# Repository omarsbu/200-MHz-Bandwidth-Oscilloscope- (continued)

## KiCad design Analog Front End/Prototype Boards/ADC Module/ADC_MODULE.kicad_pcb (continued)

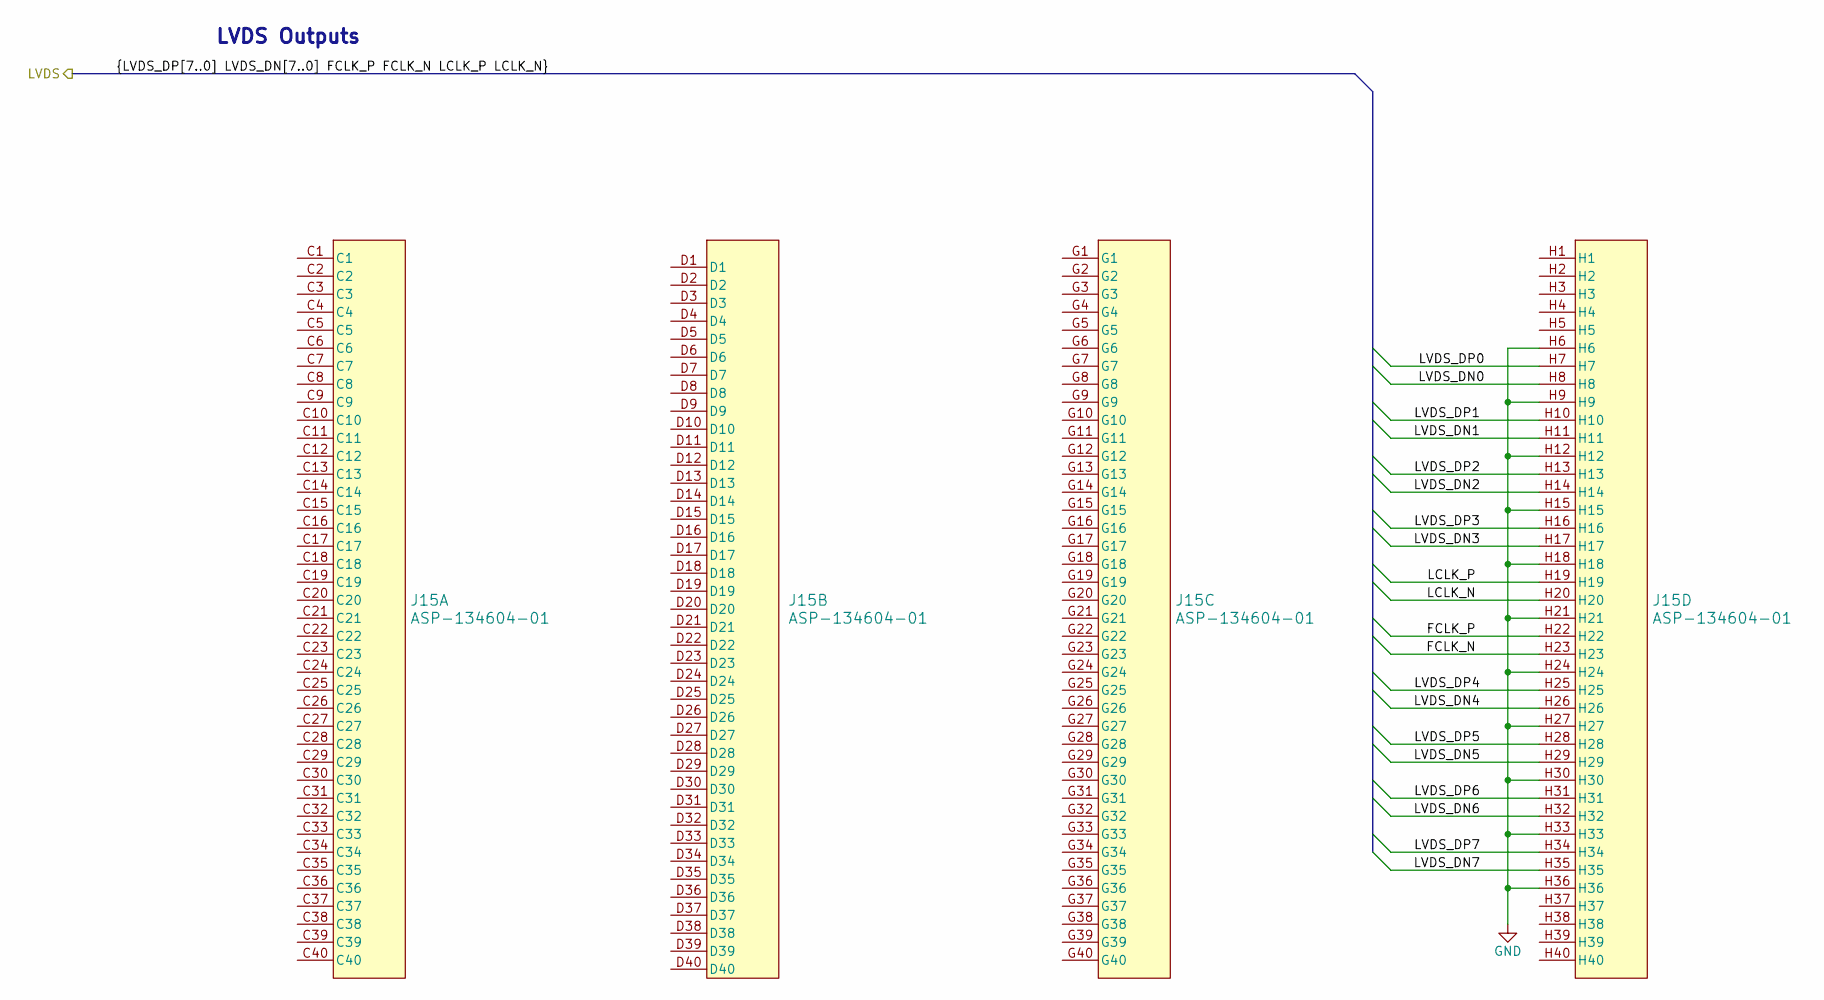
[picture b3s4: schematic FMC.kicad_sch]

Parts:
J15: ASP-134604-01; SAMTEC_ASP-134604-01

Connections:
/ADC/FCLK_N: J15.H23; also elsewhere on the board
/ADC/FCLK_P: J15.H22; also elsewhere on the board
/ADC/LCLK_N: J15.H20; also elsewhere on the board
/ADC/LCLK_P: J15.H19; also elsewhere on the board
/ADC/LVDS_DN0: J15.H8; also elsewhere on the board
/ADC/LVDS_DN1: J15.H11; also elsewhere on the board
/ADC/LVDS_DN2: J15.H14; also elsewhere on the board
/ADC/LVDS_DN3: J15.H17; also elsewhere on the board
/ADC/LVDS_DN4: J15.H26; also elsewhere on the board
/ADC/LVDS_DN5: J15.H29; also elsewhere on the board
/ADC/LVDS_DN6: J15.H32; also elsewhere on the board
/ADC/LVDS_DN7: J15.H35; also elsewhere on the board
/ADC/LVDS_DP0: J15.H7; also elsewhere on the board
/ADC/LVDS_DP1: J15.H10; also elsewhere on the board
/ADC/LVDS_DP2: J15.H13; also elsewhere on the board
/ADC/LVDS_DP3: J15.H16; also elsewhere on the board
/ADC/LVDS_DP4: J15.H25; also elsewhere on the board
/ADC/LVDS_DP5: J15.H28; also elsewhere on the board
/ADC/LVDS_DP6: J15.H31; also elsewhere on the board
/ADC/LVDS_DP7: J15.H34; also elsewhere on the board
GND: J15.H6, J15.H9, J15.H12, J15.H15, J15.H18, J15.H21, J15.H24, J15.H27, J15.H30, J15.H33, J15.H36; also elsewhere on the board

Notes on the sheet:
LVDS Outputs

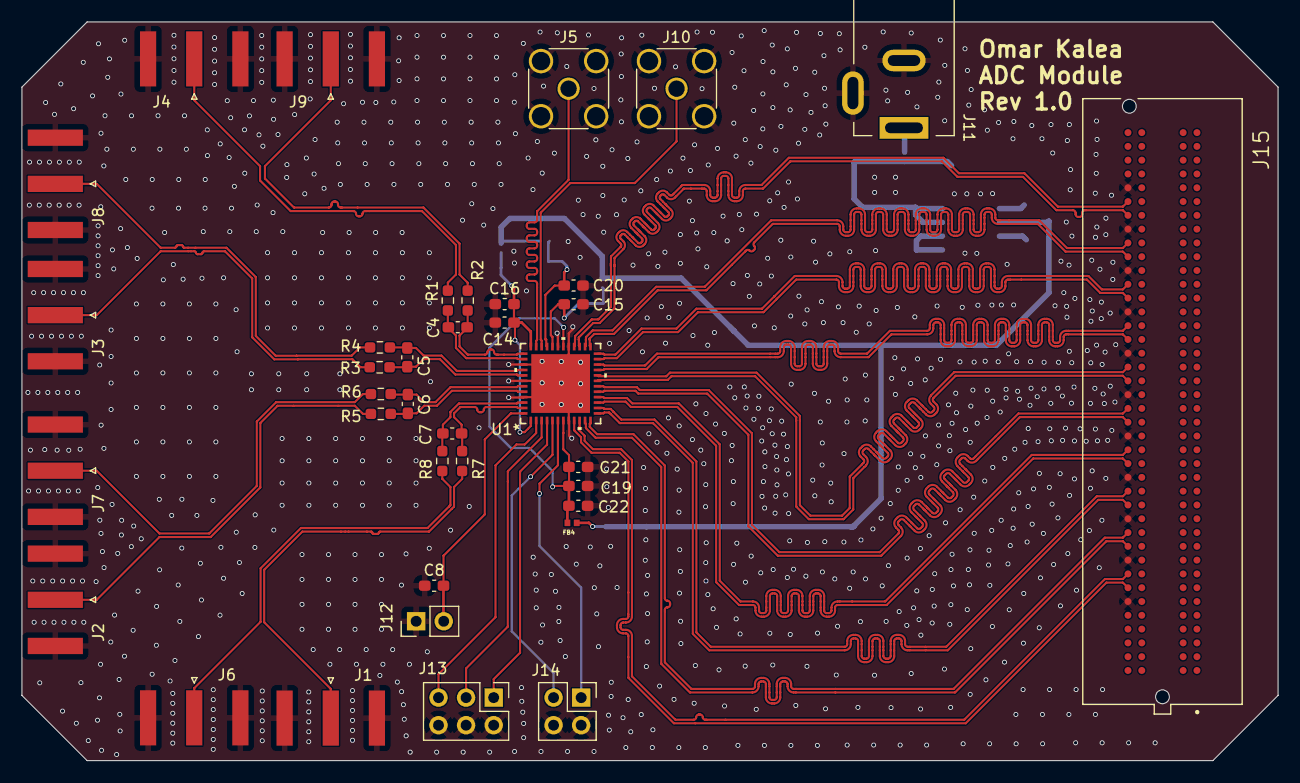
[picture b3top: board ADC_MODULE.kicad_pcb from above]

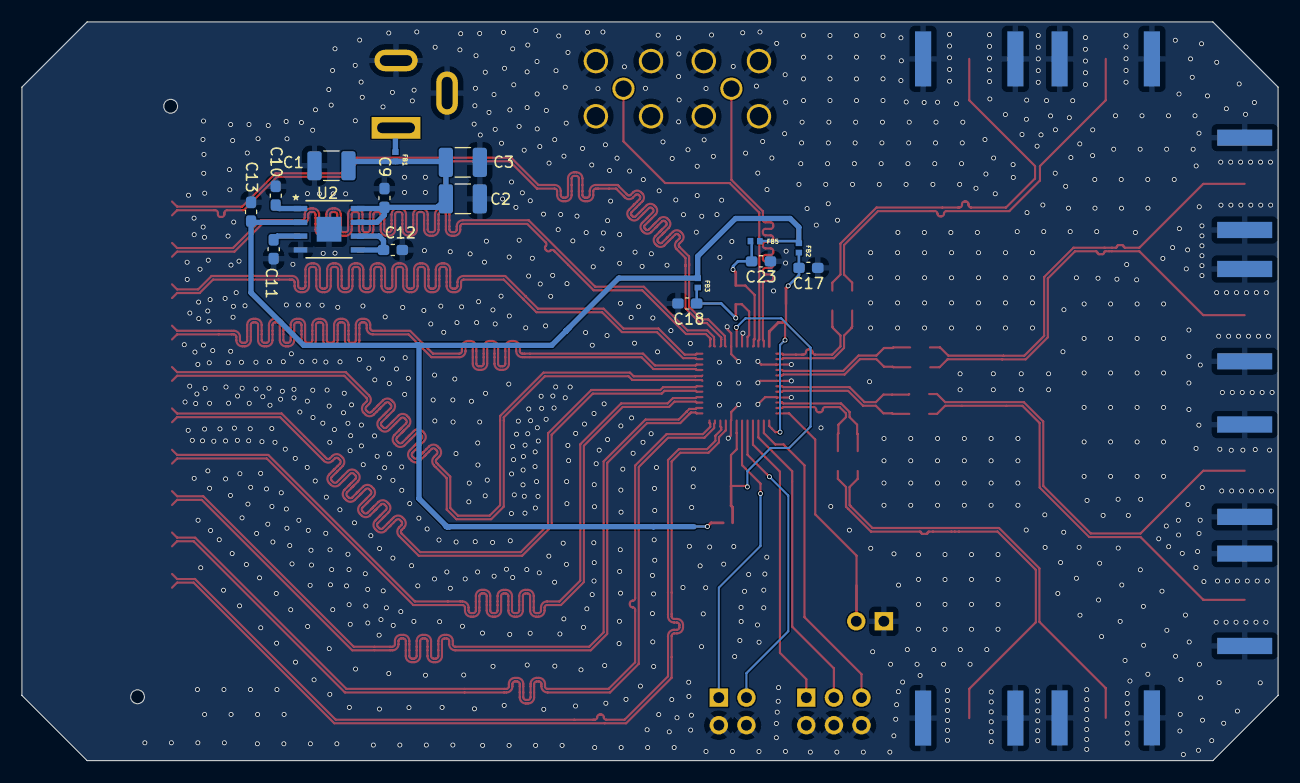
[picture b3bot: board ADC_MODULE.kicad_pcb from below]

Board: 4 copper layers, 115.7 x 68.0 mm, 53 parts (16 on the bottom side), 55 nets.

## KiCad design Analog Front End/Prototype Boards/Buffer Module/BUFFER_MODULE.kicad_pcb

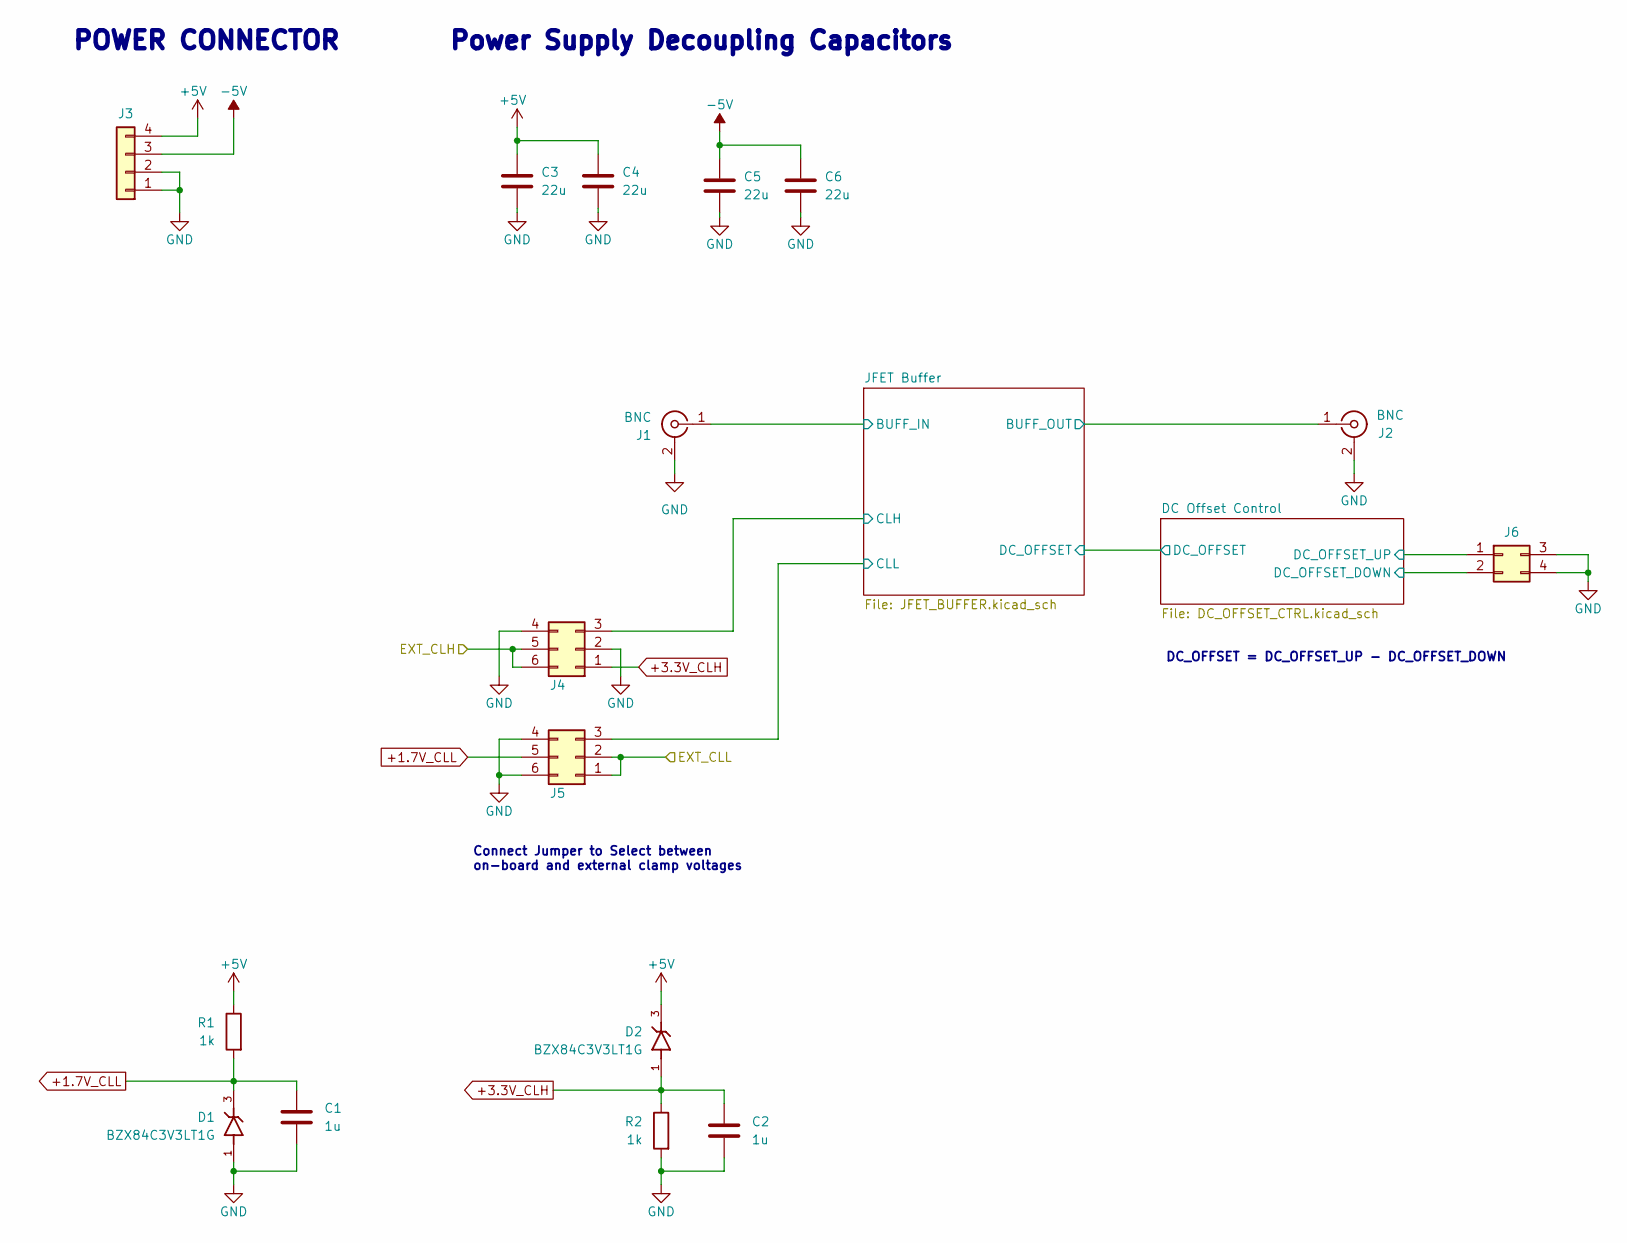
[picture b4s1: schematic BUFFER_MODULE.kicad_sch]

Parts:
C1, C2: 1u; C_0603_1608Metric
C3, C4, C5, C6: 22u; C_1210_3225Metric_Pad1.33x2.70mm_HandSolder
D1, D2: BZX84C3V3LT1G; SOT95P240X111-3N; PARTREV 23
J1, J2: BNC; CONN_73100-0105_MOL
J3: Conn_01x04; PinHeader_2x02_P2.54mm_Vertical
J4, J5: Conn_02x03_Counter_Clockwise; PinHeader_2x03_P2.54mm_Vertical
J6: Conn_02x02_Top_Bottom; PinHeader_2x02_P2.54mm_Vertical
R1, R2: 1k; R_0603_1608Metric

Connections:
+1.7V_CLL: C1.2, D1.3, J5.5, R1.2
+3.3V_CLH: C2.2, D2.1, J4.1, R2.1
+5V: C3.1, C4.1, D2.3, J3.4, R1.1; also elsewhere on the board
-5V: C5.1, C6.1, J3.3; also elsewhere on the board
/DC Offset Control/DC_OFFSET_DOWN: J6.2; also elsewhere on the board
/DC Offset Control/DC_OFFSET_UP: J6.1; also elsewhere on the board
/EXT_CLH: J4.5, J4.6
/EXT_CLL: J5.1, J5.2
/JFET Buffer/BUFF_IN: J1.1 (In); also elsewhere on the board
/JFET Buffer/BUFF_OUT: J2.1 (In); also elsewhere on the board
/JFET Buffer/CLH: J4.3; also elsewhere on the board
/JFET Buffer/CLL: J5.3; also elsewhere on the board
GND: C1.1, C2.1, C3.2, C4.2, C5.2, C6.2, D1.1, D1.2, D2.2, J1.2 (Ext), J1.3, J2.2 (Ext), J2.3, J3.1, J3.2, J4.2, J4.4, J5.4, J5.6, J6.3, J6.4, R2.2; also elsewhere on the board

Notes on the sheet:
Connect Jumper to Select between on-board and external clamp voltages
Power Supply Decoupling Capacitors
DC_OFFSET = DC_OFFSET_UP - DC_OFFSET_DOWN
POWER CONNECTOR

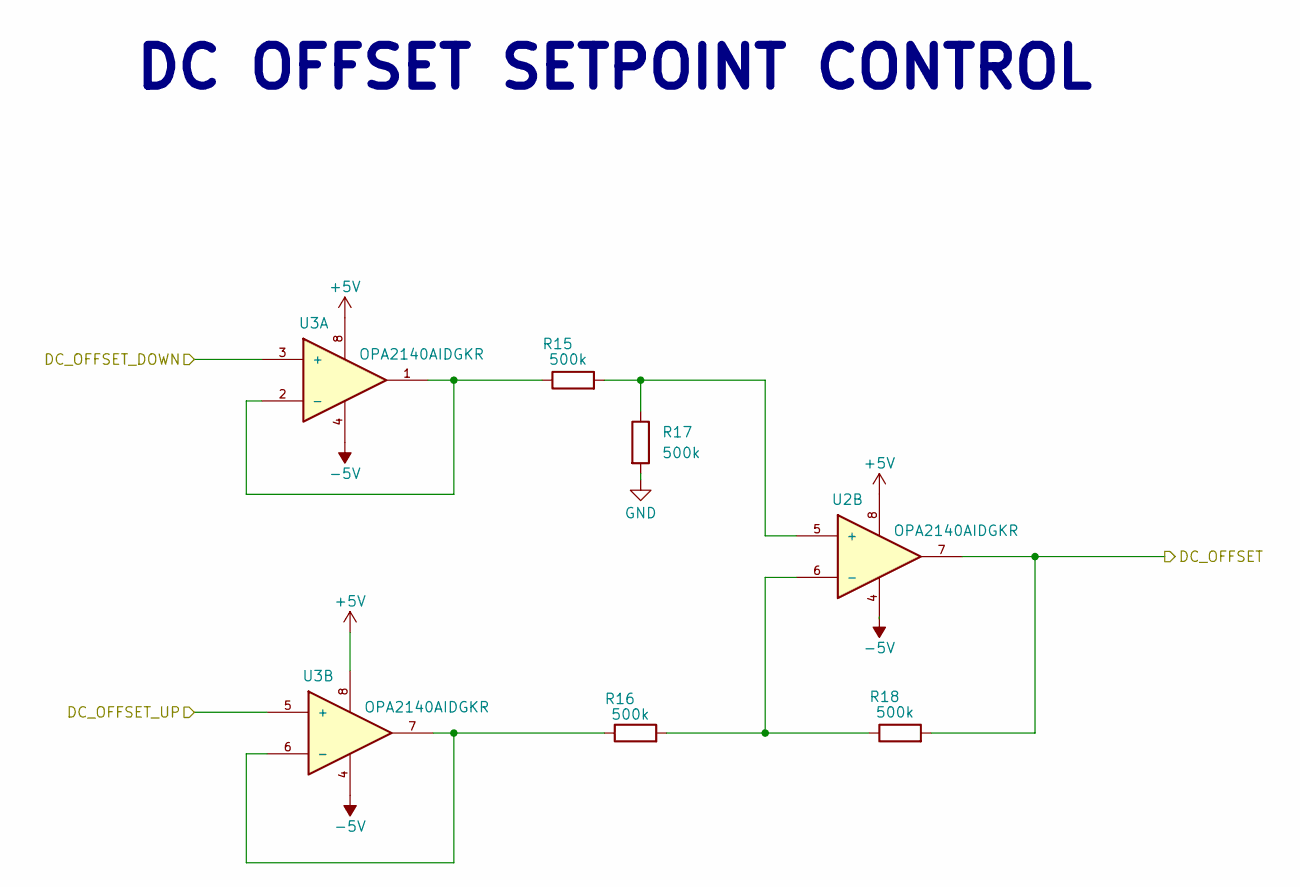
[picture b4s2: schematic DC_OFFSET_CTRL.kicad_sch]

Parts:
R15, R16, R17, R18: 500k; R_0603_1608Metric
U2, U3: OPA2140AIDGKR; DGK8; DigiKey_Part_Number 296-46321-1-ND

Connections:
+5V: U2.8, U3.8; also elsewhere on the board
-5V: U2.4, U3.4; also elsewhere on the board
/DC Offset Control/DC_OFFSET: R18.2, U2.7; also elsewhere on the board
/DC Offset Control/DC_OFFSET_DOWN: U3.3 (+); also elsewhere on the board
/DC Offset Control/DC_OFFSET_UP: U3.5 (+); also elsewhere on the board
GND: R17.2; also elsewhere on the board
unnamed: R15.2, R17.1, U2.5 (+)
unnamed: R16.2, R18.1, U2.6 (-)
unnamed: R15.1, U3.1, U3.2 (-)
unnamed: R16.1, U3.6 (-), U3.7

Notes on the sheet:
DC OFFSET SETPOINT CONTROL

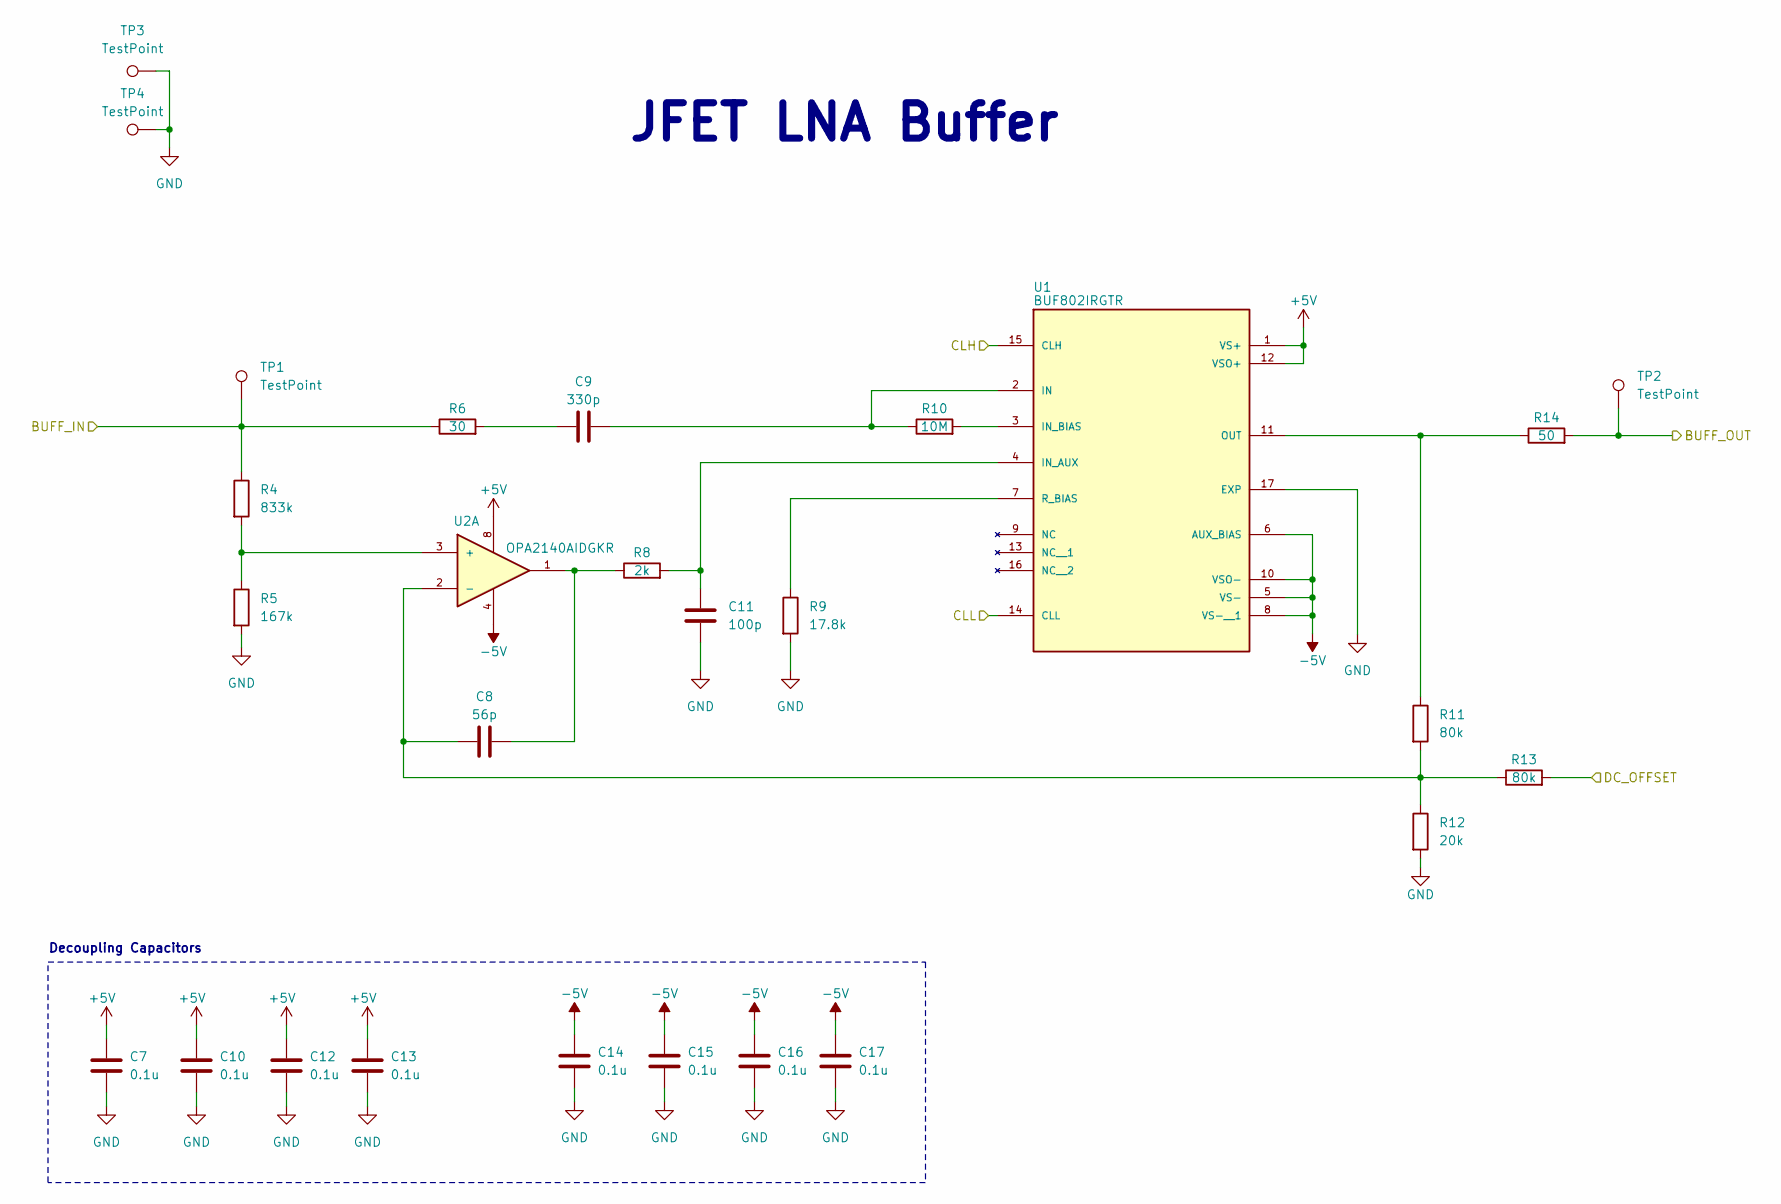
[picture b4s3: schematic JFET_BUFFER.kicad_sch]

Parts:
C7, C10, C12, C13, C14, C15, C16, C17: 0.1u; C_0603_1608Metric
C8: 56p; C_0603_1608Metric
C9: 330p; C_0603_1608Metric
C11: 100p; C_0603_1608Metric
R4: 833k; R_0603_1608Metric
R5: 167k; R_0603_1608Metric
R6: 30; R_0603_1608Metric
R8: 2k; R_0603_1608Metric
R9: 17.8k; R_0603_1608Metric
R10: 10M; R_0603_1608Metric
R11, R13: 80k; R_0603_1608Metric
R12: 20k; R_0603_1608Metric
R14: 50; R_0603_1608Metric
TP1, TP2, TP3, TP4: TestPoint; TestPoint_Pad_1.5x1.5mm
U1: BUF802IRGTR; VQFN16_RGT_TEX; PARTREV C
U2: OPA2140AIDGKR; DGK8; DigiKey_Part_Number 296-46321-1-ND

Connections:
+5V: C7.1, C10.1, C12.1, C13.1, U1.1 (VS+), U1.12 (VSO+), U2.8; also elsewhere on the board
-5V: C14.1, C15.1, C16.1, C17.1, U1.5 (VS-), U1.6 (AUX_BIAS), U1.8 (VS-__1), U1.10 (VSO-), U2.4; also elsewhere on the board
/DC Offset Control/DC_OFFSET: R13.2; also elsewhere on the board
/JFET Buffer/BUFF_IN: R4.1, R6.1, TP1.1; also elsewhere on the board
/JFET Buffer/BUFF_OUT: R14.2, TP2.1; also elsewhere on the board
/JFET Buffer/CLH: U1.15 (CLH); also elsewhere on the board
/JFET Buffer/CLL: U1.14 (CLL); also elsewhere on the board
GND: C7.2, C10.2, C11.1, C12.2, C13.2, C14.2, C15.2, C16.2, C17.2, R5.2, R9.2, R12.2, TP3.1, TP4.1, U1.17 (EXP); also elsewhere on the board
unnamed: C8.2, R8.1, U2.1
unnamed: C9.1, R6.2
unnamed: C9.2, R10.1, U1.2 (IN)
unnamed: C11.2, R8.2, U1.4 (IN_AUX)
unnamed: R10.2, U1.3 (IN_BIAS)
unnamed: R11.1, R14.1, U1.11 (OUT)
unnamed: R9.1, U1.7 (R_BIAS)
unnamed: R4.2, R5.1, U2.3 (+)
unnamed: C8.1, R11.2, R12.1, R13.1, U2.2 (-)

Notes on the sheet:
JFET LNA Buffer
Decoupling Capacitors

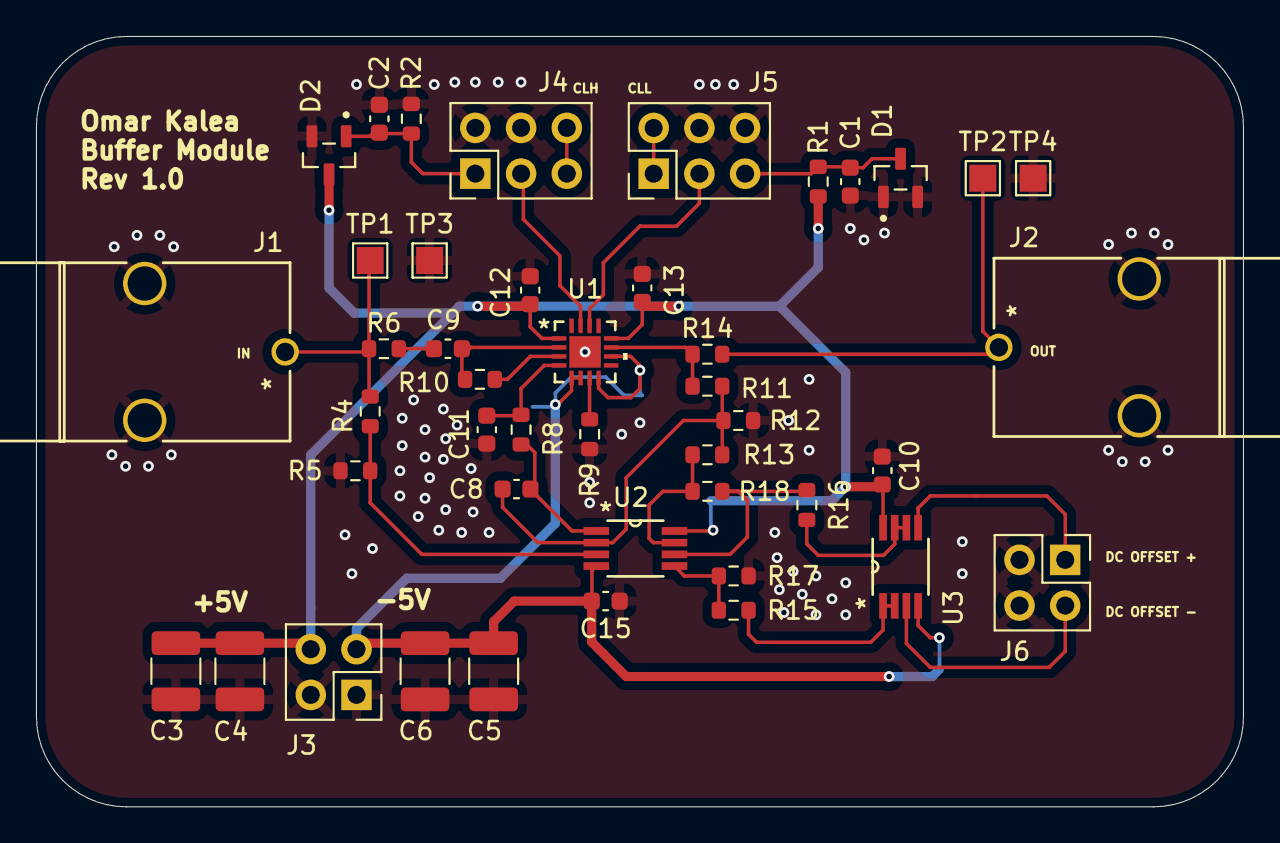
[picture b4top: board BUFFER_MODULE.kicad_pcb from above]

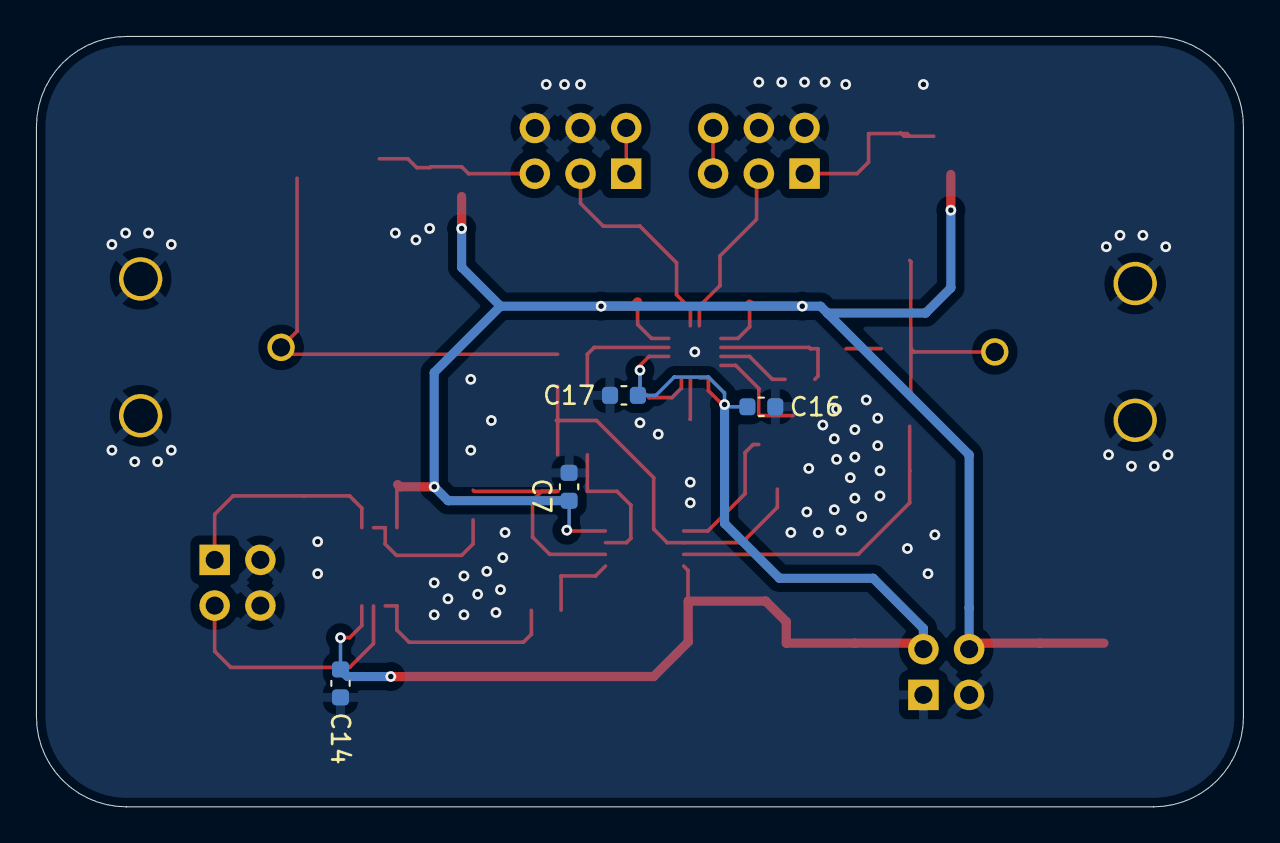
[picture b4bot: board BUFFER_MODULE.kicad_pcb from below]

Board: 4 copper layers, 67.1 x 42.8 mm, 48 parts (4 on the bottom side), 27 nets.

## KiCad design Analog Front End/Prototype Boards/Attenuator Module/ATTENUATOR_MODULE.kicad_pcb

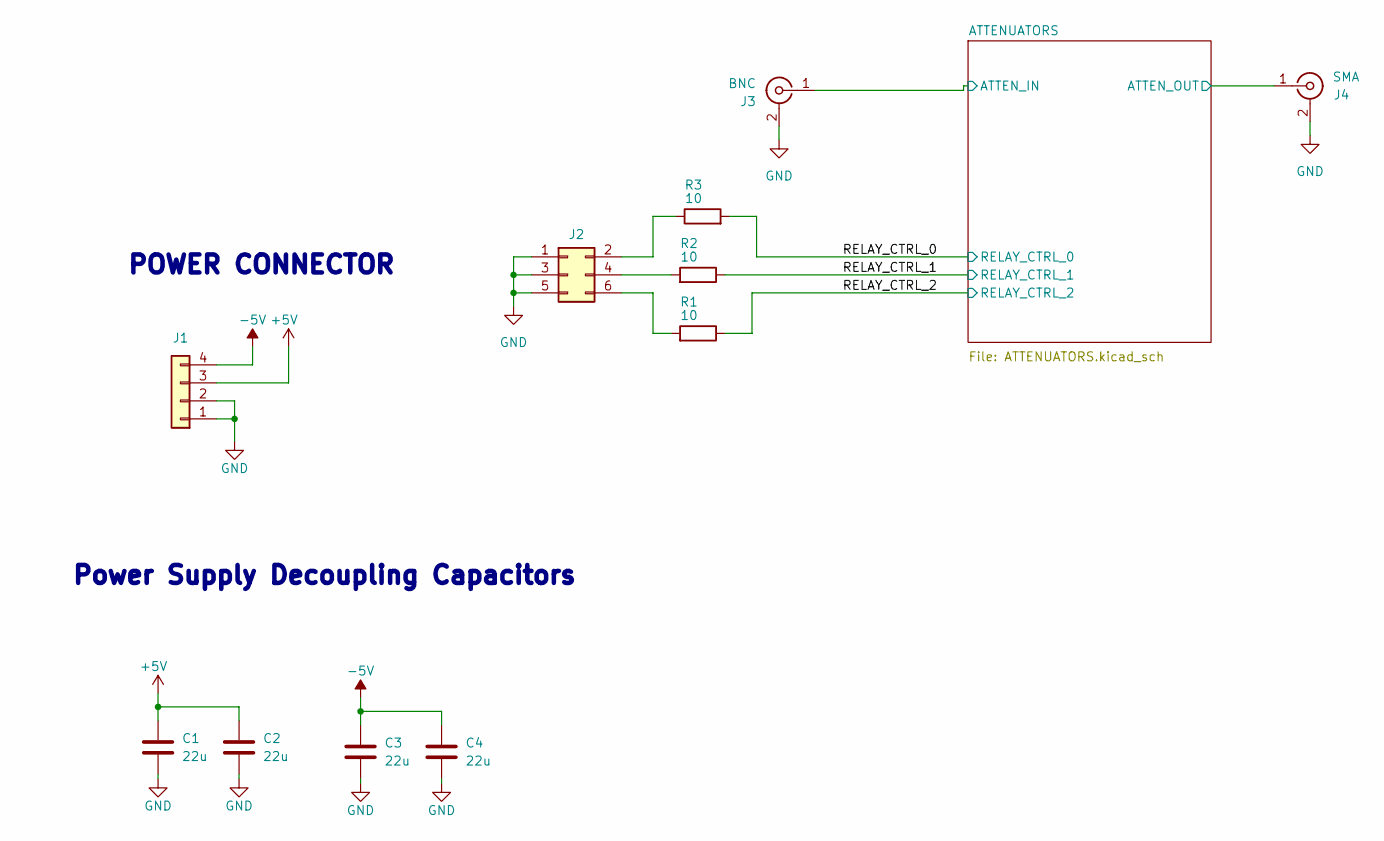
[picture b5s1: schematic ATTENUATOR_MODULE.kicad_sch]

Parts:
C1, C2, C3, C4: 22u; C_1210_3225Metric_Pad1.33x2.70mm_HandSolder
J1: Conn_01x04; PinHeader_2x02_P2.54mm_Vertical
J2: Conn_02x03_Odd_Even; PinHeader_2x03_P2.54mm_Vertical
J3: BNC; CONN_73100-0105_MOL
J4: SMA; SAMTEC_SMA-J-P-H-ST-EM1
R1, R2, R3: 10; R_0603_1608Metric

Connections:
+5V: C1.1, C2.1, J1.3; also elsewhere on the board
-5V: C3.1, C4.1, J1.4; also elsewhere on the board
/ATTENUATORS/ATTEN_IN: J3.1 (In); also elsewhere on the board
/ATTENUATORS/ATTEN_OUT: J4.1 (In); also elsewhere on the board
/RELAY_CTRL_0: R3.2; also elsewhere on the board
/RELAY_CTRL_1: R2.1; also elsewhere on the board
/RELAY_CTRL_2: R1.1; also elsewhere on the board
GND: C1.2, C2.2, C3.2, C4.2, J1.1, J1.2, J2.1, J2.3, J2.5, J3.2 (Ext), J3.3, J4.2 (Ext), J4.2_1, J4.2_2, J4.3_1, J4.3_2; also elsewhere on the board
unnamed: J2.2, R3.1
unnamed: J2.4, R2.2
unnamed: J2.6, R1.2

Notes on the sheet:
POWER CONNECTOR
Power Supply Decoupling Capacitors

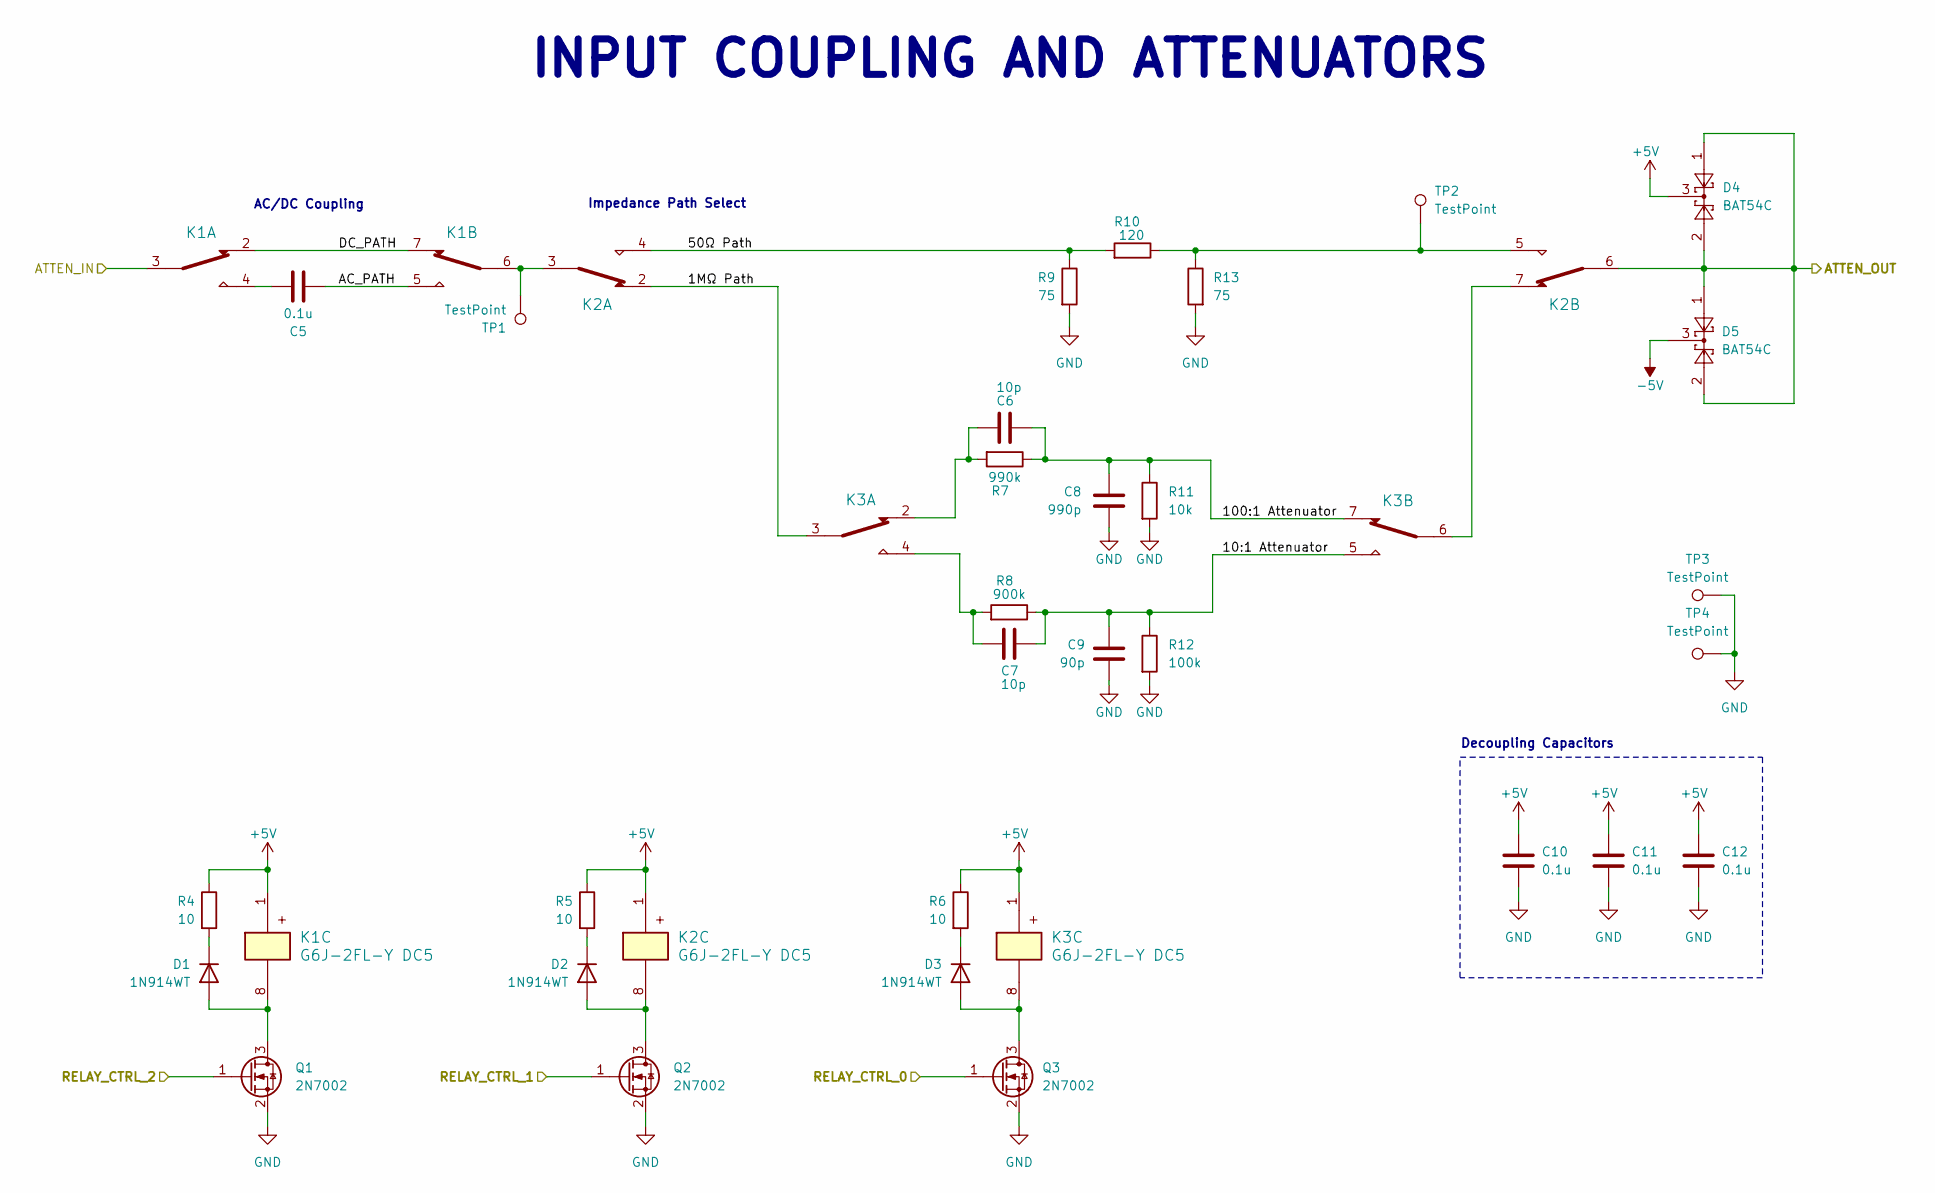
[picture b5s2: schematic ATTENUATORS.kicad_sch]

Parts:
C5, C10, C11, C12: 0.1u; C_0603_1608Metric
C6, C7: 10p; C_0603_1608Metric
C8: 990p; C_0603_1608Metric
C9: 90p; C_0603_1608Metric
D1, D2, D3: 1N914WT; D_SOD-523
D4, D5: BAT54C; SOT-23
K1, K2, K3: G6J-2FL-Y DC5; RELAY_G6J-2FL-Y DC3_OMR
Q1, Q2, Q3: 2N7002; SOT-23
R4, R5, R6: 10; R_0603_1608Metric
R7: 990k; R_0603_1608Metric
R8: 900k; R_0603_1608Metric
R9, R13: 75; R_0603_1608Metric
R10: 120; R_0603_1608Metric
R11: 10k; R_0603_1608Metric
R12: 100k; R_0603_1608Metric
TP1, TP2, TP3, TP4: TestPoint; TestPoint_Pad_1.5x1.5mm

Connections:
+5V: C10.1, C11.1, C12.1, D4.3, K1.1, K2.1, K3.1, R4.1, R5.1, R6.1; also elsewhere on the board
-5V: D5.3; also elsewhere on the board
/ATTENUATORS/1MΩ Path: K2.2, K3.3
/ATTENUATORS/10:1 Attenuator: C7.1, C9.1, K3.5, R8.1, R12.1
/ATTENUATORS/50Ω Path: K2.4, R9.1, R10.2
/ATTENUATORS/100:1 Attenuator: C6.1, C8.1, K3.7, R7.1, R11.1
/ATTENUATORS/AC_PATH: C5.1, K1.5
/ATTENUATORS/ATTEN_IN: K1.3; also elsewhere on the board
/ATTENUATORS/ATTEN_OUT: D4.1, D4.2, D5.1, D5.2, K2.6; also elsewhere on the board
/ATTENUATORS/DC_PATH: K1.2, K1.7
/RELAY_CTRL_0: Q3.1 (G); also elsewhere on the board
/RELAY_CTRL_1: Q2.1 (G); also elsewhere on the board
/RELAY_CTRL_2: Q1.1 (G); also elsewhere on the board
GND: C8.2, C9.2, C10.2, C11.2, C12.2, Q1.2 (S), Q2.2 (S), Q3.2 (S), R9.2, R11.2, R12.2, R13.2, TP3.1, TP4.1; also elsewhere on the board
unnamed: C5.2, K1.4
unnamed: C6.2, K3.2, R7.2
unnamed: C7.2, K3.4, R8.2
unnamed: D1.2 (A), K1.8, Q1.3 (D)
unnamed: D1.1 (K), R4.2
unnamed: D2.2 (A), K2.8, Q2.3 (D)
unnamed: D2.1 (K), R5.2
unnamed: D3.2 (A), K3.8, Q3.3 (D)
unnamed: D3.1 (K), R6.2
unnamed: K1.6, K2.3, TP1.1
unnamed: K2.5, R10.1, R13.1, TP2.1
unnamed: K2.7, K3.6

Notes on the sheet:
AC/DC Coupling
Decoupling Capacitors
INPUT COUPLING AND ATTENUATORS
Impedance Path Select

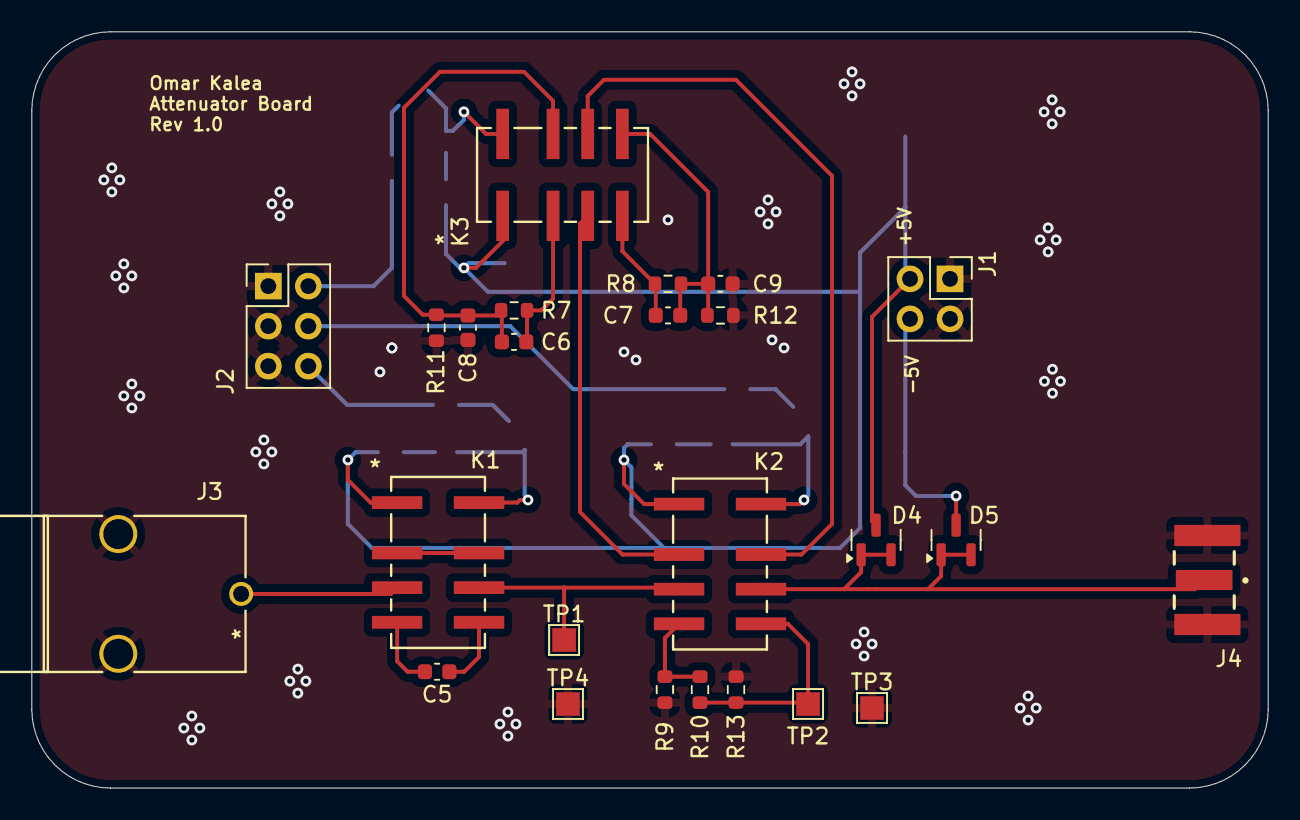
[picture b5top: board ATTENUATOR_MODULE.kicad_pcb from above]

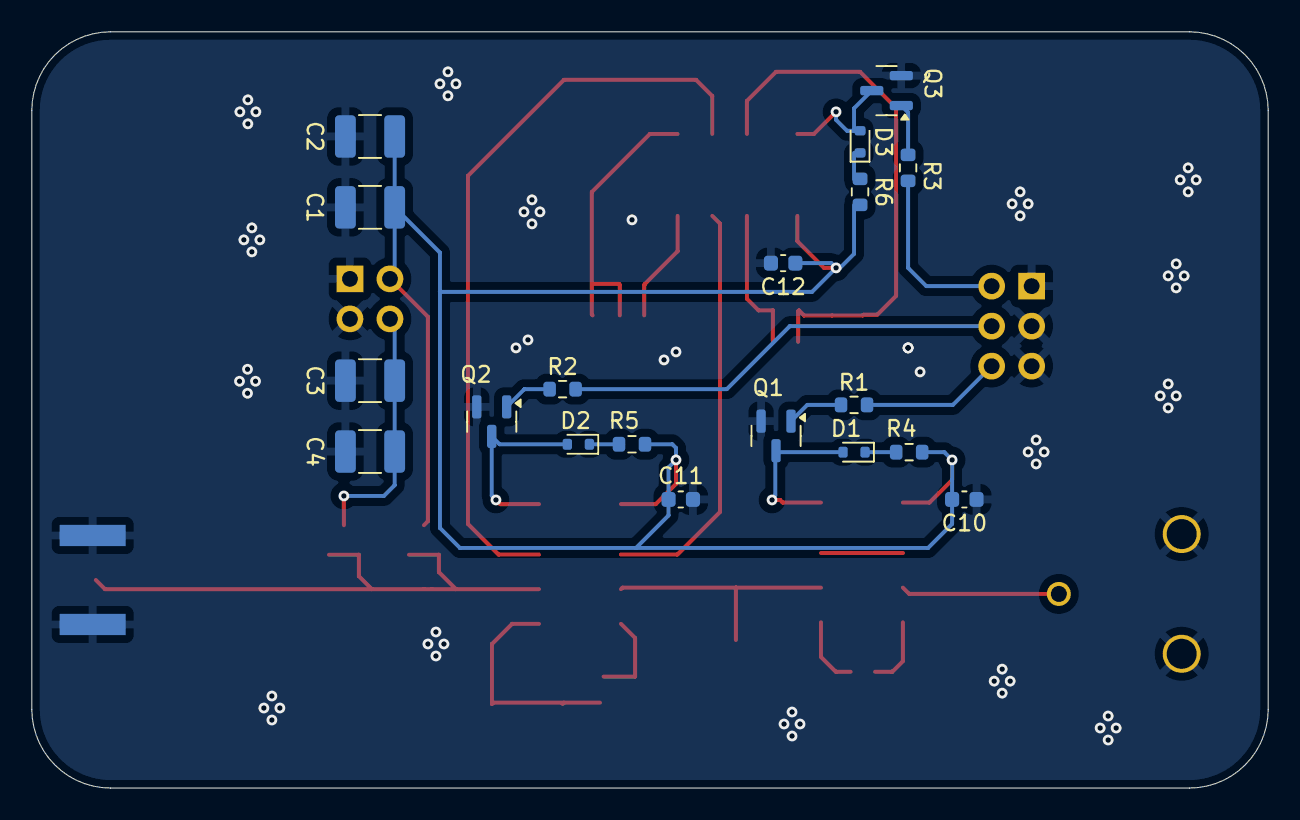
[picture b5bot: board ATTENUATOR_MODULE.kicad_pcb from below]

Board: 4 copper layers, 78.5 x 48.0 mm, 44 parts (19 on the bottom side), 29 nets.
